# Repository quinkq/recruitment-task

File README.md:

Compact, battery-powered electronic device that controls a relay for switching an 110/240 VAC 6A load.

I. Description
This circuit is a compact battery-powered system based on an ATmega328P microcontroller that can monitor battery
voltage, control a relay, and provide user interaction through buttons and status indicators. The design emphasizes low
power consumption with a voltage regulator to provide stable power to the microcontroller.
Power Supply
- Three 1.5V AAA batteries connected in series provide 4.5V input power
- MCP1700 low-dropout regulator (U3) converts the battery voltage to a stable 3.3V for the microcontroller
- Decoupling capacitors (C1, C2, C3, C7) ensure clean power delivery
Microcontroller
- ATmega328P in TQFP package (U1) serves as the main controller
- Reset circuit with push button (SW2) and pull-up resistor (R7) allows for manual resets
- Analog input connected to a voltage divider monitors battery level
- Digital I/O pins control external components
Output Control
- Relay (K1) allows switching of external high-voltage/high-current loads
- Optocoupler (PC817, U2) provides electrical isolation between the microcontroller and relay driver
- NPN transistor (2N3904, Q2) amplifies the control signal to drive the relay coil
- Protection diode (1N4007, D2) prevents inductive kickback when the relay is de-energized
- LED indicator (D1) provides visual status feedback
User Interface
- Push button input (SW1) allows for user interaction
- LED output provides visual feedback on system status

II. Control: Microcontroller ATMEL ATmega328P
1. Low Power
- Active mode: ~5mA at 3.3V, 8MHz
- Power-down sleep mode: <1μA (with proper power management)
- If running at 1MHz, it can drop active current below 1mA.
- Sleep modes allow long battery life
2. Simple and Cheap
- Readily available and has a huge ecosystem of code and libraries.
- Modular
- Cost-efficient.
3. Adequate Performance for the Task
- 10-bit ADC sufficient for battery voltage monitoring.
- Computing power more than sufficient for current project requirements.
- Enough flash and RAM (32KB Flash / 2KB RAM) for basic sensor logging and control logic.
4. Ease of Development and Debugging
- Arduino-compatible for quick prototyping.
- Analog and digital pin flexibility (for sensing battery, controlling relays, etc.) - makes it great choice for further
project adaptations.
- AVR ISP / UPDI flashing - can be pre-programmed before soldering.
In current configuration assuming pulling up unused digital pins and running by using internal oscillator.
Considerations:
STM32L0 series (for example STM32L011K or other low power variant) is a very strong contender for an alternative MCU.
It could offer substantial processing power increase (modern Cortex-M0 32-bit processor), allow for easy integrations if
for example wireless communication was considered for the future, but also opens possibility for even cheaper
components when ordering in bulk/partnering with STM.
If low power chip with integrated Bluetooth LE was a requirement from the start, then nRF52832 is another great option.
Employing wireless functionality in any of these variants would make for an attractive product to compete with SONOFF
products for example.

III. Power source: 3 x AAA batteries + LDO regulator
Due to the requirement of having battery powered controlling device, that will be inherently ineffective when driving a
power-hungry coil of the relay, the simplest solution has been chosen in form of using 3 x AAA batteries. They are
designed to be connected in series, in order to boost voltage to 4.5V, which is then shifted down to MCU and relay
compatible 3.3V level using LDO regulator. Since it’s unlikely that any compact battery will be able to power circuit
satisfying the requirements for more than 7 days, choosing AAA battery was crucial due to ease of their replacement.
1. High popularity and availability
2. Very easy to replace
3. Relatively high capacity, but dependent on the quality of batteries (about 1200 mAh)
4. Enables possibility to commercially distribute the device without batteries (passing this requirement on to the
consumer)
Considerations:
Since this project would likely be used as a device used for switching mains power supply, then most logical would be
adding a switching power supply and filtering its output to power both MCU and relay coil, instead of using batteries.
For more premium devices (relay switching noise unwanted) double MOSFET (totem pole) configuration would be a
great solution, that could be actually run with batteries. If heat dissipation or low volume were critical factors, then it
would still be possible, but would require choosing more high-end MOSFET with lower Rds(on).

IV. Components, calculations, values.
All components have been chosen with the goal of being easily sourceable and replaceable. With further testing
adjustments towards limiting optocoupler and transistor current could and should be made, as that would allow
further energy savings.
Capacitors: All ceramic for decoupling purposes, values according to chip manufacturer’s guidelines.
Resistors: Same principle with exception of:
R2 = 1000 Ohms = 3.3 V / 0.0025 A – limiting current to about 2.5 mA, enough for BJT transistor operation.
R3 = 560 Ohms = 3.3 V / 0.005 A – goal of limiting opto-coupler current down to about 5 mA, to keep small overhead in
case of PC817 current transfer ratio drops.
R4 = 150 Ohms = 3.3 V – 1.2 V / 0.0025 A – goal to maintain about 15mA LED current, assuming standard diode’s 1.2 Vf.
Dependent on final components.
R5 = 36 kOhm R6 = 100kOhm – typical voltage divider for ADC that is designed to take 3.3V as a reference (AREF pin
grounded with C4 capacitor).
Vadc = Vbat × R6/ (R5+R6)
3.3V = 4.5V x R2 / (R5+R6)
R6 / (R5+R6) = 3.3V / 4.5V = 0.733
R6 = 0.733 × (R5+R6)
Designating R6 to be 100 kOhm and solving for R5:
R5 = (100 kOhm / 0.733) − 100kΩ ≈ 36 kOhm

V. Battery life
Assuming high current draw in 30% of the time - device idling (50% of the time) and off time when toggling relay.
ATmega328P Current Consumption
Active Mode (when relay is ON): ~5mA
Sleep Mode (when relay is OFF): ~0.1mA
Relay Consumption
ON (30% of the time): ~20mA – nominal relay current ~ 70mA
OFF (70% of the time): 0mA
Other consumers
Optocoupler + transistor sinking: 7.5mA
Average Current Calculation
(5mA+20mA+7.5mA) × 30% + (0.1mA) × 70% =
= (32.5mA × 30%) + (0.1mA × 70%) =
= 9.75mA + 0.07mA = 9.82 mA
Battery Life (1200mAh AAA in series)
1200 mAh ÷ (~9.82mA) = 122 hours = about 5 days

VI. Costs
Details in BOM.csv.
Estimate for making 5 pieces:
10,16 USD
Estimate for making 1000 pieces:
4,20 USD

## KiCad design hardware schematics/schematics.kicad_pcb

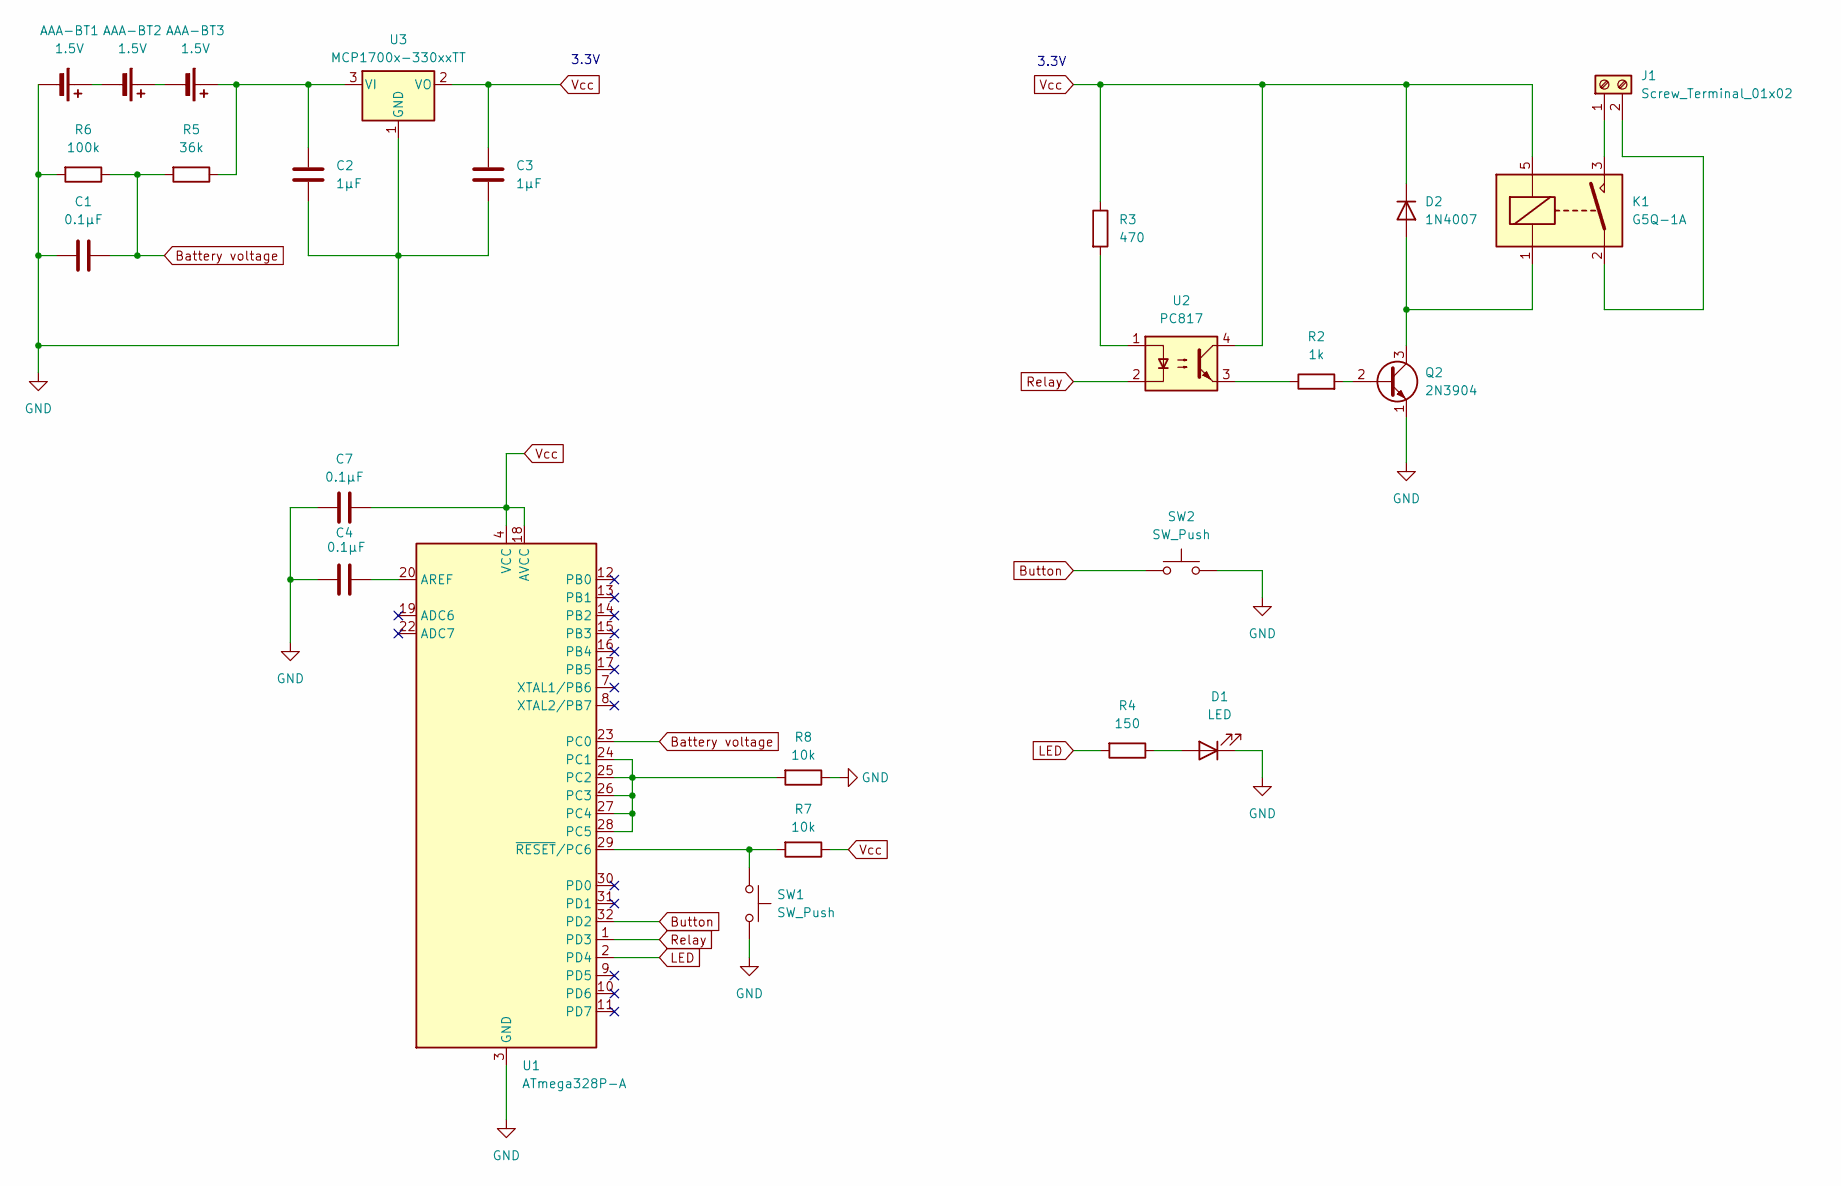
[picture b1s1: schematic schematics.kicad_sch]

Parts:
AAA-BT1, AAA-BT2, AAA-BT3: 1.5V; BatteryHolder_Keystone_2466_1xAAA
C1, C4, C7: 0.1µF; C_0805_2012Metric
C2, C3: 1µF; C_0805_2012Metric
D1: LED; LED_D3.0mm_FlatTop
D2: 1N4007; D_DO-41_SOD81_P10.16mm_Horizontal
J1: Screw_Terminal_01x02; TerminalBlock_Phoenix_MKDS-1,5-2_1x02_P5.00mm_Horizontal
K1: G5Q-1A; Relay_SPST_Omron-G5Q-1A
Q2: 2N3904; TO-92_Inline
R2: 1k; R_0805_2012Metric
R3: 470; R_0805_2012Metric
R4: 150; R_0805_2012Metric
R5: 36k; R_0805_2012Metric
R6: 100k; R_0805_2012Metric
R7, R8: 10k; R_0805_2012Metric
SW1: SW_Push; SW_SPST_CK_RS282G05A3
SW2: SW_Push; SW_SPST_PTS647_Sx70
U1: ATmega328P-A; TQFP-32_7x7mm_P0.8mm
U2: PC817; DIP-4_W7.62mm
U3: MCP1700x-330xxTT; SOT-23

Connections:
Battery voltage: C1.2, R5.2, R6.1, U1.23 (PC0)
Button: SW2.1, U1.32 (PD2)
GND: AAA-BT1.2 (-), C1.1, C2.1, C3.1, C4.1, C7.1, D1.1 (K), Q2.1 (E), R6.2, R8.1, SW1.2, SW2.2, U1.3 (GND), U1.5 (GND), U1.21 (GND), U3.1 (GND)
LED: R4.2, U1.2 (PD4)
unnamed: AAA-BT1.1 (+), AAA-BT2.2 (-)
unnamed: AAA-BT2.1 (+), AAA-BT3.2 (-)
unnamed: AAA-BT3.1 (+), C2.2, R5.1, U3.3 (VI)
unnamed: D1.2 (A), R4.1
unnamed: D2.2 (A), K1.1, Q2.3 (C)
unnamed: J1.1, K1.3
unnamed: J1.2, K1.2
unnamed: Q2.2 (B), R2.2
unnamed: R2.1, U2.3
unnamed: R3.2, U2.1
unnamed: C4.2, U1.20 (AREF)
unnamed: R8.2, U1.24 (PC1), U1.25 (PC2), U1.26 (PC3), U1.27 (PC4), U1.28 (PC5)
unnamed: R7.2, SW1.1, U1.29 (~RESET/PC6)
Relay: U1.1 (PD3), U2.2
Vcc: C3.2, C7.2, D2.1 (K), K1.5, R3.1, R7.1, U1.4 (VCC), U1.6 (VCC), U1.18 (AVCC), U2.4, U3.2 (VO)

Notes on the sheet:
3.3V

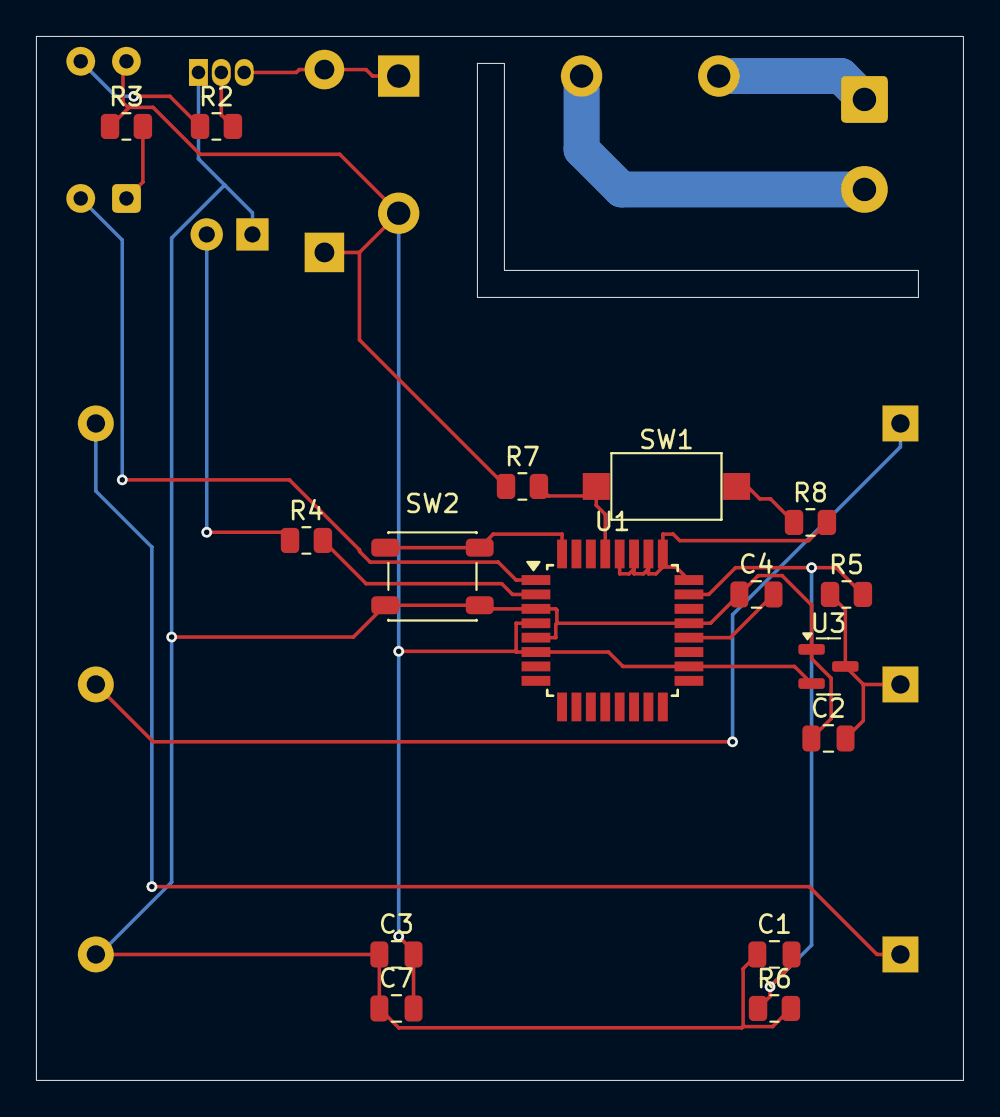
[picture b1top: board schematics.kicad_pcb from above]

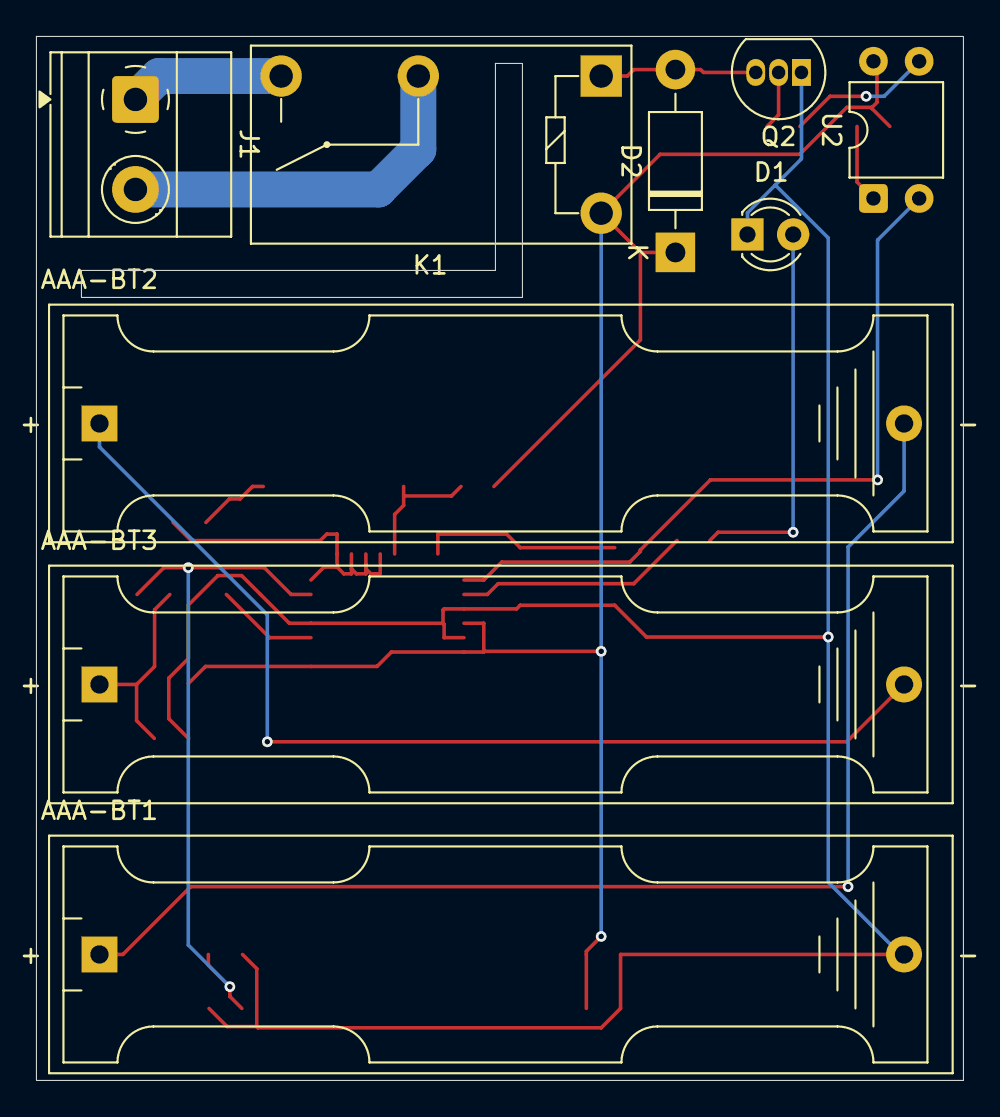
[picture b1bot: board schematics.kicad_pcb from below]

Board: 2 copper layers, 51.5 x 58.0 mm, 25 parts (9 on the bottom side), 19 nets.

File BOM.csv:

Reference;Qty;Value;Footprint;Price (1pc);Sum for (1pc price);Price (1000pcs);Sum for (1000pc price) [USD];Datasheet
AAA-BT1,AAA-BT2,AAA-BT3;3;1.5V;Battery:BatteryHolder_Keystone_2466_1xAAA;0,52;0,52;0,333;0,333;~
C1,C4,C7;3;0.1µF;Capacitor_SMD:C_0805_2012Metric;0,004;0,012;0,0036;0,0108;~
C2,C3;2;1µF;Capacitor_SMD:C_0805_2012Metric;0,004;0,008;0,0036;0,0072;~
D1;1;LED;LED_THT:LED_D3.0mm_FlatTop;0,02;0,02;0,018;0,018;~
D2;1;1N4007;Diode_THT:D_DO-41_SOD81_P10.16mm_Horizontal;0,008;0,008;0,005;0,005;http://www.vishay.com/docs/88503/1n4001.pdf
J1;1;Screw_Terminal_01x02;TerminalBlock_Phoenix:TerminalBlock_Phoenix_MKDS-1,5-2_1x02_P5.00mm_Horizontal;0,0894;0,0894;0,0591;0,0591;~
K1;1;G5Q-1A;Relay_THT:Relay_SPST_Omron-G5Q-1A;0,9036;0,9036;0,5468;0,5468;https://www.omron.com/ecb/products/pdf/en-g5q.pdf
Q2;1;2N3904;Package_TO_SOT_THT:TO-92_Inline;0,0115;0,0115;0,0077;0,0077;https://www.onsemi.com/pub/Collateral/2N3903-D.PDF
R2;1;1k;Resistor_SMD:R_0805_2012Metric;0,0018;0,0018;0,0014;0,0014;~
R3;1;470;Resistor_SMD:R_0805_2012Metric;0,0018;0,0018;0,0014;0,0014;~
R4;1;150;Resistor_SMD:R_0805_2012Metric;0,0018;0,0018;0,0014;0,0014;~
R5;1;36k;Resistor_SMD:R_0805_2012Metric;0,0018;0,0018;0,0014;0,0014;~
R6;1;100k;Resistor_SMD:R_0805_2012Metric;0,0018;0,0018;0,0014;0,0014;~
R7,R8;2;10k;Resistor_SMD:R_0805_2012Metric;0,0018;0,0036;0,0014;0,0028;~
SW1;1;SW_Push;Button_Switch_SMD:SW_SPST_CK_RS282G05A3;0,796;0,796;0,2918;0,2918;~
SW2;1;SW_Push;Button_Switch_SMD:SW_SPST_PTS647_Sx70;0,1925;0,1925;0,1243;0,1243;~
U1;1;ATmega328P-A;Package_QFP:TQFP-32_7x7mm_P0.8mm;2,1871;2,1871;1,5494;1,5494;http://ww1.microchip.com/downloads/en/DeviceDoc/ATmega328_P%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
U2;1;PC817;Package_DIP:DIP-4_W7.62mm;0,0341;0,0341;0,0185;0,0185;http://www.soselectronic.cz/a_info/resource/d/pc817.pdf
U3;1;MCP1700x-330xxTT;Package_TO_SOT_SMD:SOT-23;0,3705;0,3705;0,2257;0,2257;http://ww1.microchip.com/downloads/en/DeviceDoc/20001826D.pdf
;;;;;;;;
PCB Manufacturing;1;;;5;5;1;1;
;;;;;Estimate for 5 pcs;;Estimate for 1000 pcs;
;;;;Total Sum;10,1683;USD;4,2071;USD
